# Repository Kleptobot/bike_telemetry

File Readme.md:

# OBike — Open Bicycle Telemetry Platform

OBike is an open-source hardware and firmware project for building a DIY bike computer that feels closer to a purpose-built cycling device than a generic microcontroller project. It combines a colour display, GPS, Bluetooth sensors, barometric altitude, and SD-card logging into a single platform you can build, modify, and improve.

If you like the idea of a compact, open bike computer that can log rides, display live metrics, and be extended with new sensors or UI ideas, this repository is a good place to start.

## What this project does

OBike is intended to capture and present ride data such as:

- speed and distance
- cadence and power
- heart rate
- GPS position and track history
- barometric altitude and sensor-derived data

It presents that information on a colour screen and can log sessions to microSD in FIT, TCX, or CSV formats.

It also supports common Bluetooth cycling peripherals that implement the CSC, HRM, and CPS profiles.

## What is in this repository

- `src/` — firmware source in C++
  - `src/App.*` — main application state and control flow
  - `src/HAL/` — hardware abstraction for GPS, SD, Bluetooth, buttons, and sensors
  - `src/ui/` — UI screens and widgets
  - `src/Loggers/` — FIT, TCX, and CSV logging implementations
  - `src/display/` — display driver and rendering wrappers
- `kicad/` — KiCad schematic and PCB layout files
- `3D_CAD/` — enclosure and mounting CAD files for 3D printing
- `sim/` — desktop simulator for trying the firmware logic without hardware
- `platformio.ini` — PlatformIO build configuration

## Hardware overview

The current hardware target is a compact embedded bike-computer build based on:

- MCU: Seeed Studio XIAO nRF52840 (Sense)
- GNSS: Quectel LC76G module
- Display: ST7789-based full-colour 240×320 SPI panel
- Sensors: RTC, barometric pressure sensor, IMU, and SD card storage
- IO: debounced physical controls and Bluetooth cycling-device support

## Quick start

### Build the firmware

1. Install PlatformIO.
2. From the repository root, run:

   ```bash
   platformio run
   ```

3. To upload to the target board:

   ```bash
   platformio run --target upload
   ```

### Try it without hardware

The repository includes a desktop simulator under `sim/` that can exercise much of the application logic and UI without needing the embedded board.

## Software features

- Firmware built with PlatformIO and the Arduino framework
- Telemetry aggregation from BLE sensors, GPS, and onboard sensors
- Logging to microSD in FIT, TCX, and CSV formats
- GPS control and NMEA handling for the LC76G module
- A simple UI for ride data and device interaction
- Bluetooth device discovery, pairing, and connection management

## Dependencies

The firmware depends on a number of Arduino and embedded libraries, including:

- `Adafruit_GFX`
- `Adafruit_ST7789`
- `MCP23017` support for the I/O expander
- `LSM6DS3`
- `XENSIV` pressure-sensor support
- `ArduinoJson`
- `TinyGPSPlus`
- `teddokano/RTC_NXP_Arduino`

## Key files to inspect

- `src/HAL/LC76G.cpp` and `src/HAL/LC76G.hpp` — GNSS driver, NMEA handling, and command flow
- `src/display/Display.hpp` and `src/display/Display.cpp` — display wrapper and rendering layer
- `src/Loggers/TCXLogger.cpp` and `src/Loggers/CSVLogger.cpp` — ride logging implementations
- `src/App.cpp` — main application loop and state handling
- `kicad/` — schematic and PCB design files
- `3D_CAD/` — printable enclosure and mounting hardware

## Troubleshooting and debugging

- Serial logs are useful during development and can help trace GPS and device activity.
- Raw NMEA data can be captured to the SD card for debugging GPS behavior.
- The LC76G path has previously been sensitive to malformed or long NMEA streams, so keeping firmware updates current is important if you hit GPS issues.

## Notes for first-time visitors

This project is best viewed as a hands-on, open-source bike-computer platform rather than a polished consumer product. It is a strong fit if you want to learn embedded firmware, PCB design, logging formats, BLE peripherals, and how a compact cycling computer can be assembled from open parts.

If you are curious about building your own ride-data device, this repository is a practical starting point for both the hardware and software sides of the project.

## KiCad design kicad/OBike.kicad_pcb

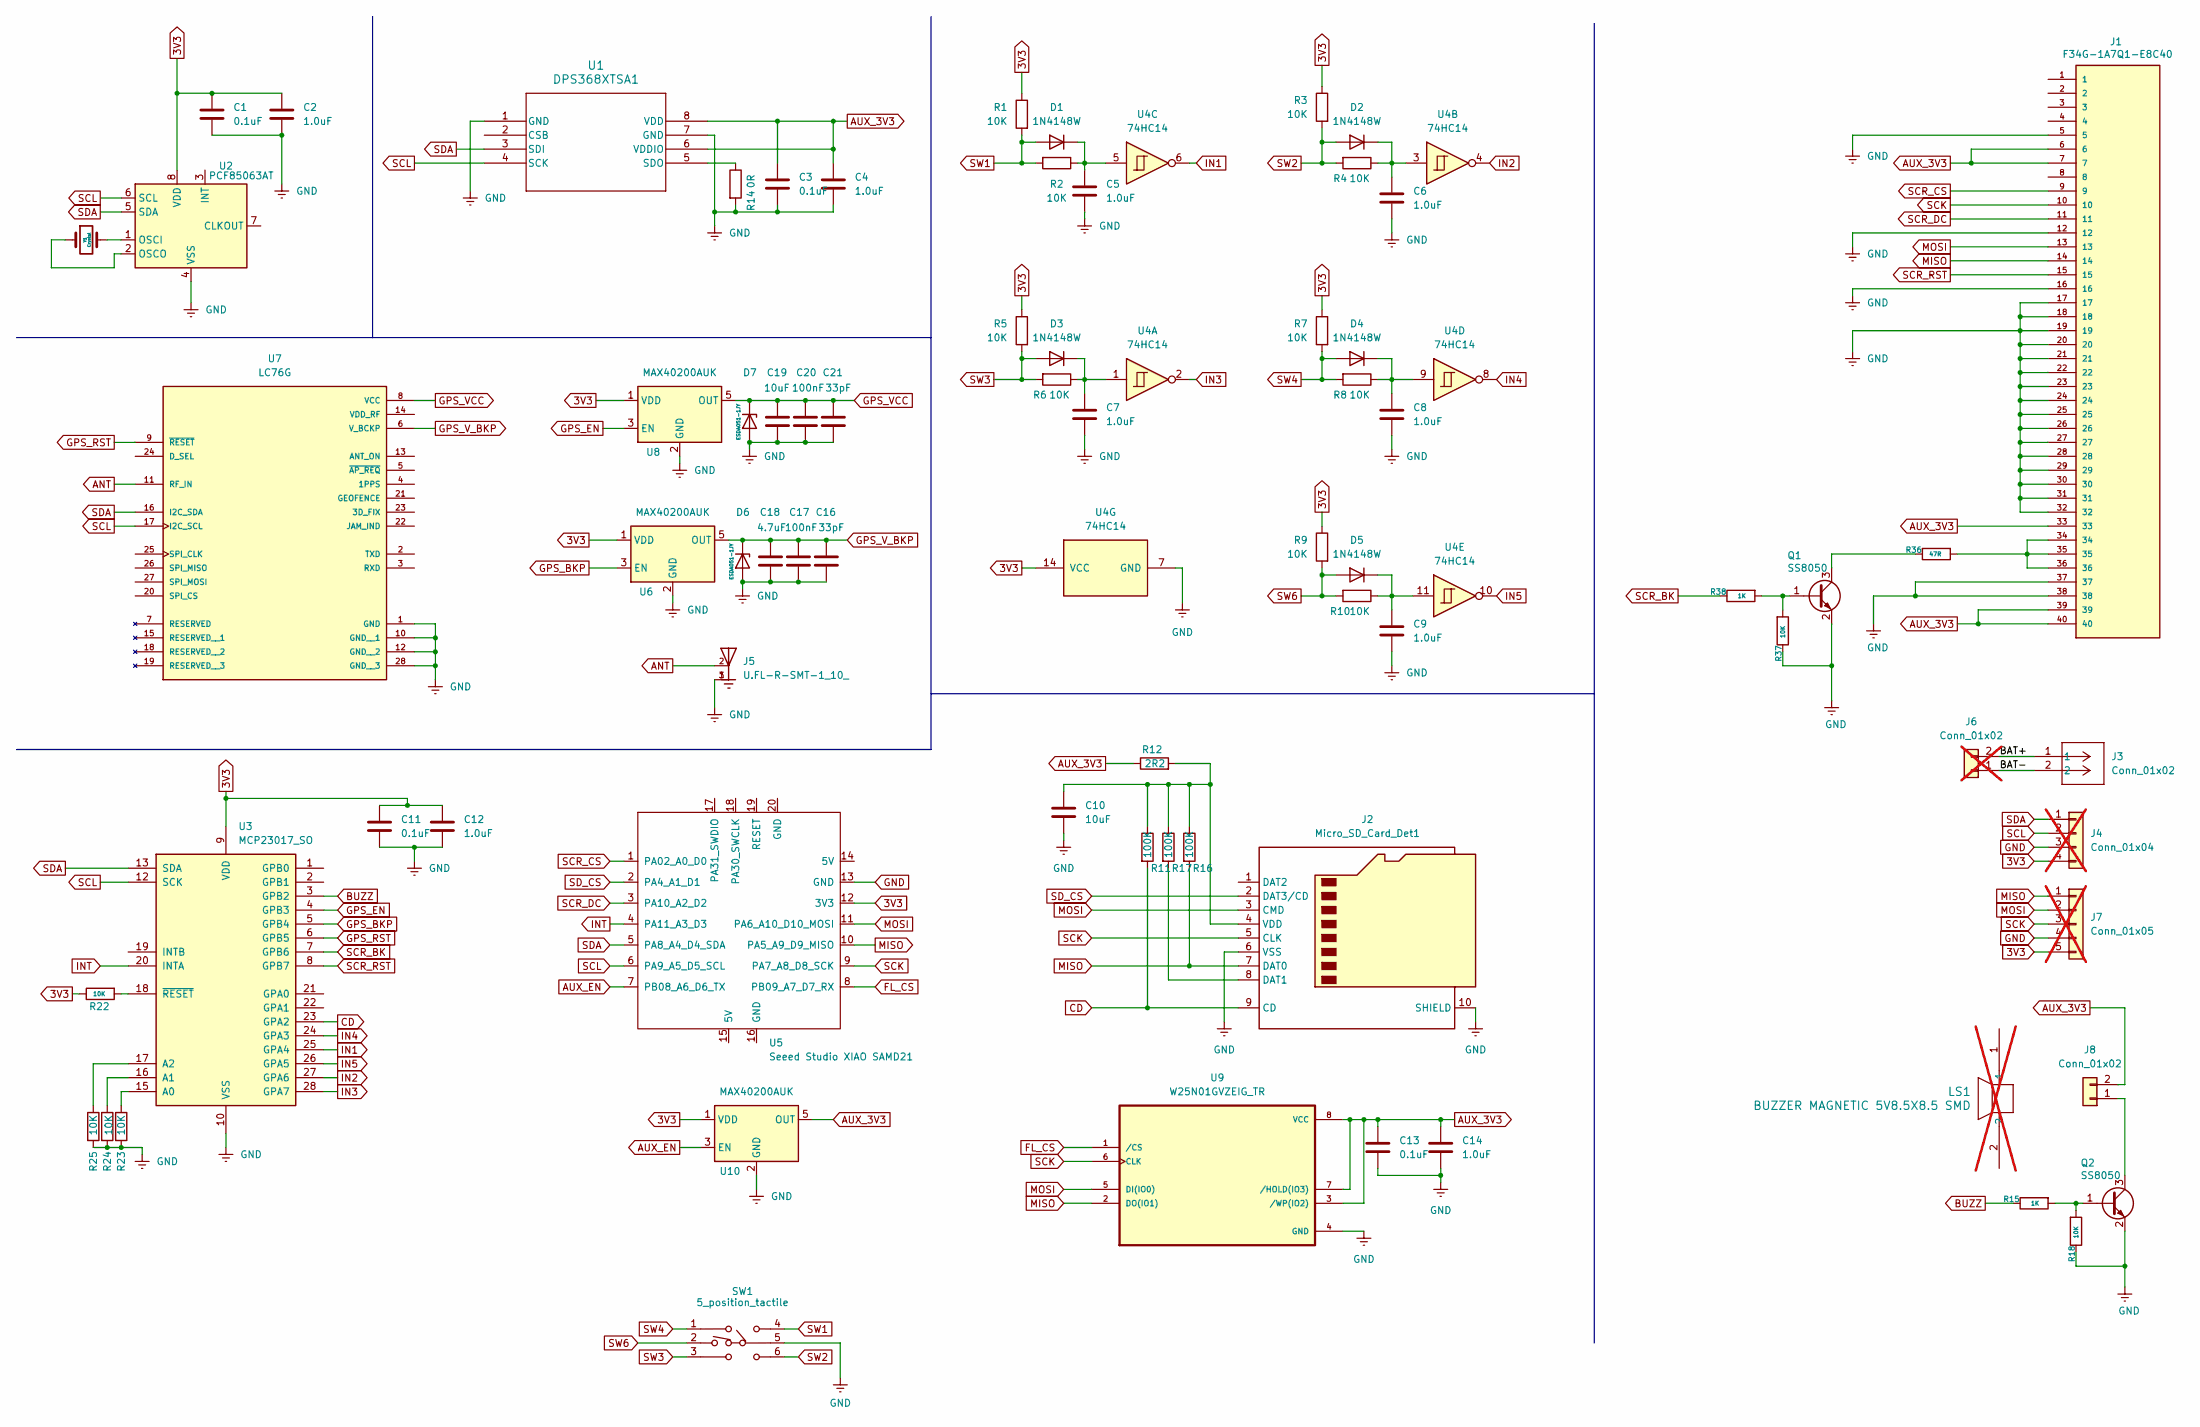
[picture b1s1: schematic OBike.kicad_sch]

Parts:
C1, C3, C11, C13: 0.1uF; C_0805_2012Metric; Digikey PN 1276-2442-1-ND
C2, C4, C5, C6, C7, C8, C9, C12, C14: 1.0uF; C_0805_2012Metric; Digikey PN 1276-1066-1-ND
C10, C19: 10uF; C_0603_1608Metric; Digikey PN 1276-1038-1-ND
C16, C21: 33pF; C_0603_1608Metric; Digikey PN 399-C0603C330K3RACTUCT-ND
C17, C20: 100nF; C_0603_1608Metric; Digikey PN 399-C0603C104K3RACTUCT-ND
C18: 4.7uF; C_0603_1608Metric; Digikey PN 1276-1044-1-ND
D1, D2, D3, D4, D5: 1N4148W; D_SOD-123; Manufacturer PN 1N4148W RHG; Digikey PN 1655-1N4148WCT-ND
D6, D7: ESDA051-1JY; D_SOD-323; Digikey PN 497-ESDA051-1JYCT-ND
J1: F34G-1A7Q1-E8C40; AMPHENOL_F34G-1A7Q1-E8C40; PARTREV A; Digikey PN 609-F34G-1A7Q1-E8C40CT-ND
J2: Micro_SD_Card_Det1; CUI_MSD-4-A; Manufacturer PN MSD-4-A; Digikey PN 2223-MSD-4-ACT-ND
J3: Conn_01x02; JST_PH_S2B-PH-K_1x02_P2.00mm_Horizontal; Manufacturer PN CONN HEADER R/A 2POS 2MM; Digikey PN 455-1719-ND
J4: Conn_01x04; PinHeader_1x04_P2.54mm_Vertical; not fitted
J5: U.FL-R-SMT-1_10_; HRS_U.FL-R-SMT-1_10_; Digikey PN H11891CT-ND
J6: Conn_01x02; PinHeader_1x02_P2.00mm_Vertical; not fitted
J7: Conn_01x05; PinHeader_1x05_P2.54mm_Vertical; not fitted
J8: Conn_01x02; PinHeader_1x02_P2.00mm_Vertical
LS1: BUZZER MAGNETIC 5V8.5X8.5 SMD; CUI_CMT-8540S-SMT; Digikey PN 102-3746-1-ND; not fitted
Q1, Q2: SS8050; SOT-23; Digikey PN MMSS8050-H-TPMSCT-ND
R1, R2, R3, R4, R5, R6, R7, R8, R9, R10, R22, R23, R24, R25: 10K; R_0805_2012Metric; Digikey PN RMCF0805JT10K0CT-ND
R11, R16, R17: 100K; R_0603_1608Metric; Digikey PN RMCF0603FT100KCT-ND
R12: 2R2; R_0603_1608Metric; Digikey PN RMCF0603FT2R20CT-ND
R14: 0R; R_0603_1608Metric
R15, R38: 1K; R_0603_1608Metric; Digikey PN RMCF0603JT1K00CT-ND
R18, R37: 10K; R_0603_1608Metric; Digikey PN RMCF0603JT10K0CT-ND
R36: 47R; R_0603_1608Metric; Digikey PN RMCF0603JT47R0CT-ND
SW1: 5_position_tactile; 5-position; Manufacturer PN 2425755-1; Digikey PN 450-2425755-1CT-ND
U1: DPS368XTSA1; PG-VLGA-8-2_INF; Manufacturer PN DPS368XTSA1; Digikey PN DPS368XTSA1CT-ND
U2: PCF85063AT; SOIC-8_3.9x4.9mm_P1.27mm; Digikey PN 568-12403-1-ND
U3: MCP23017_SO; SOIC-28W_7.5x17.9mm_P1.27mm; Manufacturer PN MCP23017T-E/SO; Digikey PN MCP23017T-E/SOCT-ND
U4: 74HC14; SOIC-14_3.9x8.7mm_P1.27mm; Manufacturer PN 74HC14D; Digikey PN 74HC14DCT-ND
U5: Seeed Studio XIAO SAMD21; XIAO-nRF52840-Sense-14P-2.54-21X17.8MM
U6, U8, U10: MAX40200AUK; SOT-23-5; Digikey PN MAX40200AUK+TCT-ND
U7: LC76G; XCVR_LC76G; PARTREV 1.0; Digikey PN 2958-LC76GPAMDCT-ND
U9: W25N01GVZEIG_TR; SON127P800X600X80-9N; Digikey PN 256-W25N01GVZEIGTRCT-ND
Y1: Crystal; OSCSC320X150X90; Digikey PN 1908-Q0,032768-JTX310-7-20-T3-80K-LFCT-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

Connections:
3V3: C1.1, C2.1, C11.1, C12.1, J4.4, J7.5, R1.1, R3.1, R5.1, R7.1, R9.1, R22.1, U2.8 (VDD), U3.9 (VDD), U4.14 (VCC), U5.12 (3V3), U6.1 (VDD), U8.1 (VDD), U10.1 (VDD)
/BAT+: J3.1, J6.2
/BAT-: J3.2, J6.1
ANT: J5.2, U7.11 (RF_IN)
AUX_3V3: C3.1, C4.1, C13.1, C14.1, J1.6, J1.7, J1.33, J1.39, J1.40, J8.2, R12.1, U1.6 (VDDIO), U1.8 (VDD), U9.3 (/WP(IO2)), U9.7 (/HOLD(IO3)), U9.8 (VCC), U10.5 (OUT)
AUX_EN: U5.7 (PB08_A6_D6_TX), U10.3 (EN)
BUZZ: R15.1, U3.3 (GPB2)
CD: J2.9 (CD), R11.2, U3.23 (GPA2)
FL_CS: U5.8 (PB09_A7_D7_RX), U9.1 (/CS)
GND: C1.2, C2.2, C3.2, C4.2, C5.2, C6.2, C7.2, C8.2, C9.2, C10.2, C11.2, C12.2, C13.2, C14.2, C16.2, C17.2, C18.2, C19.2, C20.2, C21.2, D6.2 (A), D7.2 (A), J1.5, J1.12, J1.16, J1.17, J1.18, J1.19, J1.20, J1.21, J1.22, J1.23, J1.24, J1.25, J1.26, J1.27, J1.28, J1.29, J1.30, J1.31, J1.32, J1.37, J1.38, J2.6 (VSS), J2.10 (SHIELD), J4.3, J5.1, J5.3, J7.4, Q1.2 (E), Q2.2 (E), R14.2, R18.1, R23.2, R24.2, R25.2, R37.1, SW1.5 (E), U1.1 (GND), U1.7 (GND), U2.4 (VSS), U3.10 (VSS), U4.7 (GND), U5.13 (GND), U6.2 (GND), U7.1 (GND), U7.10 (GND__1), U7.12 (GND__2), U7.28 (GND__3), U8.2 (GND), U9.4 (GND), U10.2 (GND)
GPS_BKP: U3.5 (GPB4), U6.3 (EN)
GPS_EN: U3.4 (GPB3), U8.3 (EN)
GPS_RST: U3.6 (GPB5), U7.9 (~RESET)
GPS_VCC: C19.1, C20.1, C21.1, D7.1 (K), U7.8 (VCC), U8.5 (OUT)
GPS_V_BKP: C16.1, C17.1, C18.1, D6.1 (K), U6.5 (OUT), U7.6 (V_BCKP)
IN1: U3.25 (GPA4), U4.6
IN2: U3.27 (GPA6), U4.4
IN3: U3.28 (GPA7), U4.2
IN4: U3.24 (GPA3), U4.8
IN5: U3.26 (GPA5), U4.10
INT: U3.20 (INTA), U5.4 (PA11_A3_D3)
MISO: J1.14, J2.7 (DAT0), J7.1, R16.2, U5.10 (PA5_A9_D9_MISO), U9.2 (DO(IO1))
MOSI: J1.13, J2.3 (CMD), J7.2, U5.11 (PA6_A10_D10_MOSI), U9.5 (DI(IO0))
unnamed: C5.1, D1.1 (K), R2.1, U4.5
unnamed: C6.1, D2.1 (K), R4.1, U4.3
unnamed: C7.1, D3.1 (K), R6.1, U4.1
unnamed: C8.1, D4.1 (K), R8.1, U4.9
unnamed: C9.1, D5.1 (K), R10.1, U4.11
unnamed: J1.34, J1.35, J1.36, R36.2
unnamed: J2.8 (DAT1), R17.2
unnamed: C10.1, J2.4 (VDD), R11.1, R12.2, R16.1, R17.1
unnamed: J8.1, Q2.3 (C)
unnamed: Q1.1 (B), R37.2, R38.2
unnamed: Q1.3 (C), R36.1
unnamed: Q2.1 (B), R15.2, R18.2
unnamed: R14.1, U1.5 (SDO)
unnamed: U2.1 (OSCI), Y1.2
unnamed: U2.2 (OSCO), Y1.1
unnamed: R23.1, U3.15 (A0)
unnamed: R24.1, U3.16 (A1)
unnamed: R25.1, U3.17 (A2)
unnamed: R22.2, U3.18 (~RESET)
SCK: J1.10, J2.5 (CLK), J7.3, U5.9 (PA7_A8_D8_SCK), U9.6 (CLK)
SCL: J4.2, U1.4 (SCK), U2.6 (SCL), U3.12 (SCK), U5.6 (PA9_A5_D5_SCL), U7.17 (I2C_SCL)
SCR_BK: R38.1, U3.7 (GPB6)
SCR_CS: J1.9, U5.1 (PA02_A0_D0)
SCR_DC: J1.11, U5.3 (PA10_A2_D2)
SCR_RST: J1.15, U3.8 (GPB7)
SDA: J4.1, U1.3 (SDI), U2.5 (SDA), U3.13 (SDA), U5.5 (PA8_A4_D4_SDA), U7.16 (I2C_SDA)
SD_CS: J2.2 (DAT3/CD), U5.2 (PA4_A1_D1)
SW1: D1.2 (A), R1.2, R2.2, SW1.4 (D)
SW2: D2.2 (A), R3.2, R4.2, SW1.6 (F)
SW3: D3.2 (A), R5.2, R6.2, SW1.3 (C)
SW4: D4.2 (A), R7.2, R8.2, SW1.1 (A)
SW6: D5.2 (A), R9.2, R10.2, SW1.2 (B)

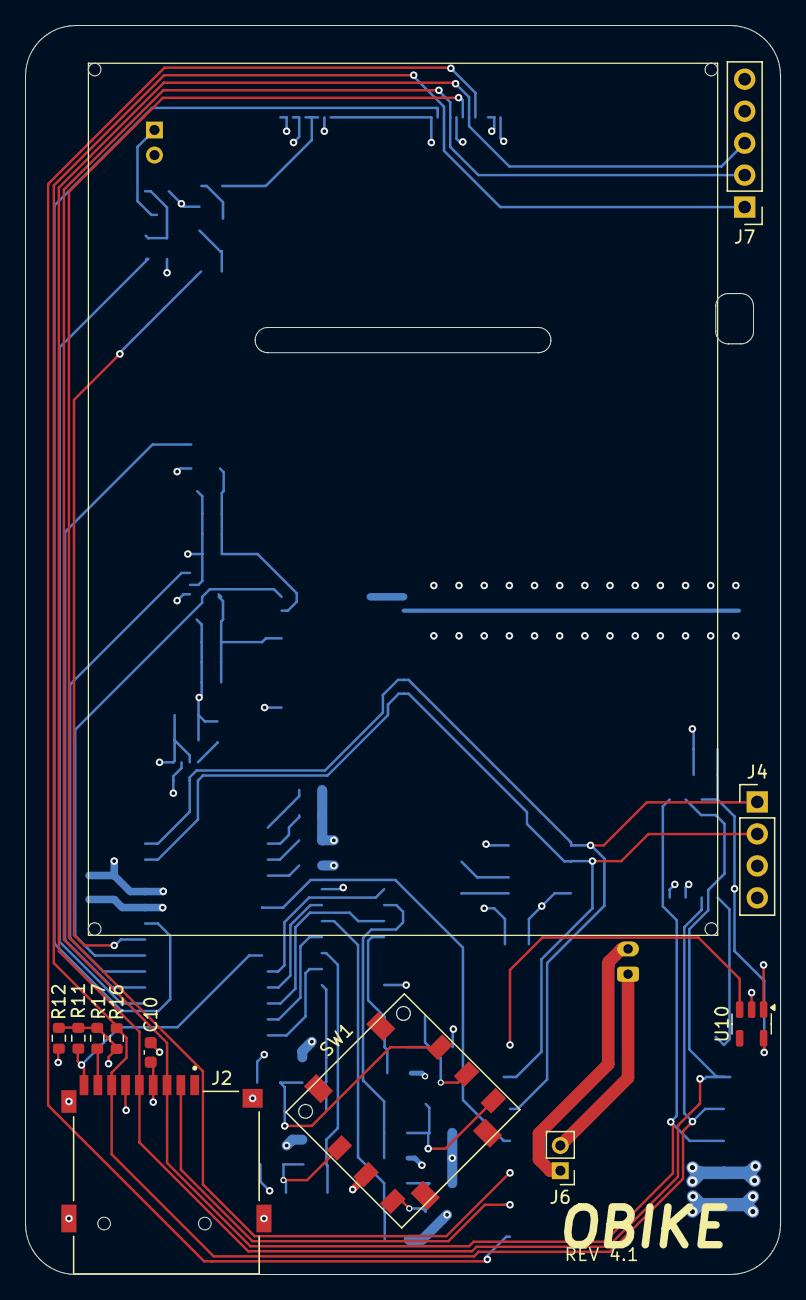
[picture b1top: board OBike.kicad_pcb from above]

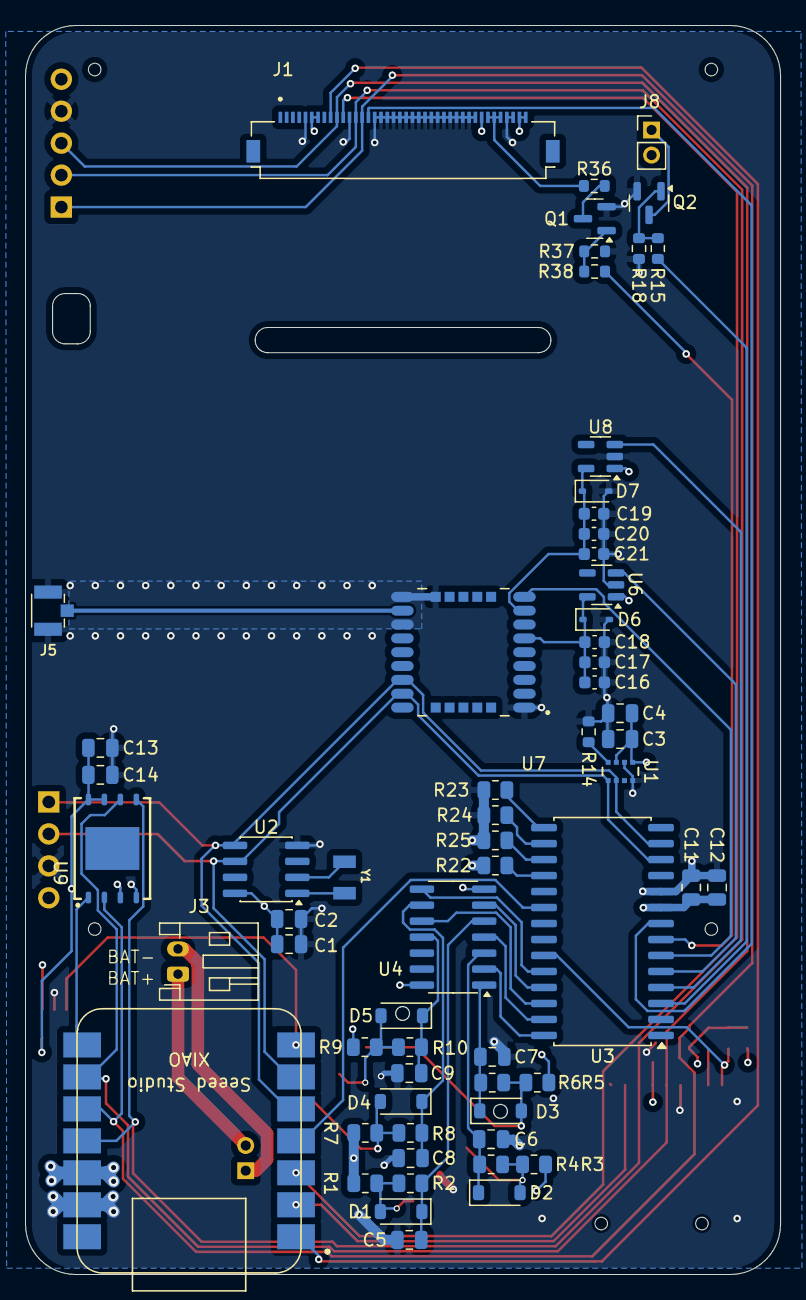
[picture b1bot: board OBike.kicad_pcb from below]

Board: 4 copper layers, 60.0 x 99.2 mm, 73 parts (62 on the bottom side), 55 nets.

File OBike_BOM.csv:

"Reference","Value","Datasheet","Footprint","Qty","DNP","PARTREV","Manufacturer PN","Manufacturer","Digikiey PN"
"AE1","Antenna","~","Antenna:AC30036-01","1","","","AC30036-01","The Antenna Company","5350-AC30036-01-ND"
"C1,C3,C11","0.1uF","~","Capacitor_SMD:C_0805_2012Metric","3","","","","",""
"C2,C4,C5,C6,C7,C8,C9,C12","1.0uF","~","Capacitor_SMD:C_0805_2012Metric","8","","","","",""
"C10","10uF","~","Capacitor_SMD:C_0603_1608Metric","1","","","","",""
"D1,D2,D3,D4,D5","1N4148W","https://www.vishay.com/docs/85722/1n4448w.pdf","Diode_SMD:D_SOD-123","5","","","1N4148W RHG","Taiwan Semiconductor Corporation","1N4148WRHGCT-ND"
"J1","Conn_01x08","~","Connector_JST:JST_GH_SM08B-GHS-TB_1x08-1MP_P1.25mm_Horizontal","1","","","","",""
"J2","Micro_SD_Card_Det1","https://datasheet.lcsc.com/lcsc/2110151630_XKB-Connectivity-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","CUI-devices:CUI_MSD-11-A","1","","","MSD-11-A","Same Sky (Formerly CUI Devices)","2223-MSD-11-ACT-ND"
"J3,J6","Conn_01x02","-- mixed values --","-- mixed values --","2","","","-- mixed values --","-- mixed values --","-- mixed values --"
"R1,R2,R3,R4,R5,R6,R7,R8,R9,R10,R16,R22,R23,R24,R25","10K","~","-- mixed values --","15","","","","",""
"R11,R15,R17","100K","~","Resistor_SMD:R_0603_1608Metric","3","","","","",""
"R12","2R2","~","Resistor_SMD:R_0603_1608Metric","1","","","","",""
"R13,R14","0R","~","Resistor_SMD:R_0603_1608Metric","2","","","","",""
"SW1","5_position_tactile","~","5_pos:5-position","1","","","2425755-1","TE Connectivity ALCOSWITCH Switches","450-2425755-1CT-ND"
"U1","DPS368XTSA1","DPS368XTSA1","Infineon Technologies:PG-VLGA-8-2_INF","1","","","DPS368XTSA1","Infineon Technologies","DPS368XTSA1CT-ND"
"U2","DS3231M","http://datasheets.maximintegrated.com/en/ds/DS3231.pdf","Package_SO:SOIC-8_3.9x4.9mm_P1.27mm","1","","","DS3231MZ+","Analog Devices Inc./Maxim Integrated","DS3231MZ+-ND"
"U3","MCP23017_SO","http://ww1.microchip.com/downloads/en/DeviceDoc/20001952C.pdf","Package_SO:SOIC-28W_7.5x17.9mm_P1.27mm","1","","","MCP23017T-E/SO","Microchip Technology","MCP23017T-E/SOCT-ND"
"U4","74HC14","http://www.ti.com/lit/gpn/sn74HC14","Package_SO:SOIC-14_3.9x8.7mm_P1.27mm","1","","","74HC14D","Toshiba Semiconductor and Storage","74HC14DCT-ND"
"U5","Seeed Studio XIAO SAMD21","","xiao:XIAO-nRF52840-Sense-14P-2.54-21X17.8MM","1","","","","",""
"U6","MAX-M8C-0","","uBlox:XCVR_MAX-M8C-0","1","","R06, 27-May-2020","MAX-M8C-0","u-blox","672-MAX-M8C-0CT-ND"

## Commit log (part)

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2024-04-30 Initial code checkin
2024-04-30 electrical
2024-04-30 renaming .ino
2024-04-30 renaming folder structure
2024-04-30 adding millis to logging
2024-06-29 kicad libraries
    added symbols and footprints.
    put library files in dedicated folder
2024-06-29 Added PCB files
    added kicad project files
2024-06-29 License and Readme
    added the readme file updated license
2024-06-29 fixing pcb references
    changed references to combined board to Obike in the PCB file
2024-06-29 Readme to markdown
2024-06-29 1.69" TFT
    Changed screen connections to suit an SPI screen
    Changed the arduino project to use the adafruit ST7789 library
    Intended LCD is the wavshare 1.69" LCD
2024-07-01 adding dsp368 to project
2024-07-12 moved setup back into setup
2024-07-12 sh1107
2024-07-22 using SDFat library now
    log files are now named the datastamp of when the log was started
2024-07-23 bugfixes
    fixed bug where speed available and cadence available where not set to 0 on csc begin
    added timer to main screen when logging
    seperated out devices init into seperate function that is only called if the wake interrupt has been triggered
    cadence now displayed as an integer
2024-07-24 fixed logging bug
    fixed bug that stopped data being written to log
    added functions to write tail data at the end of a log
    now calculate average and max speed
    using the sd card detection pin to reinit sd card when re-inserted
2024-08-05 bug fixes
    added lost power time reset for rtc
    changed device save file to json
    added delay after power on before loading devices from SD
    now wait a bit between connecting to multiple devices
    split draw method and ui method for BT screen
    bt devices now remain selected for storage
2024-08-07 batt disp
    added battery service to csc class
    added logging to sd card
    battery now displays on bt menu
    can now turn off obike by holding down button
2024-08-10 connection issue fix
    - fixed up scanning logic so start scan is not being called too often
    - connection and battery symbols only displayed for stored devices
    - stored symbol does not display for non stored devices
    - connection handle is stored for discovered devices
    - added disconnect callback
    - logger can now accept strings
2024-08-12 Update bike_telemetry.ino
    support for more devices in bt devices view
2024-08-18 BT device polymorphism
    Created base class of BT_Device
    csc now extends BT_Device
    created hrm class which extends BT_Device
2024-08-20 Added cps
    fixed bugs in BT_Device implementation
2024-08-25 Bug fixing
    removing BT devices no longer causes crashes
    upped the number of data sources able to be logged
    changed most uses of String to char*
    heartrate now shows on main screen
2024-08-25 device scanning fixes
    scanning now starts for stored devices
    discovered devices now identified as the correct type
    hrm battery service now started correctly
2024-09-01 moved SD instance to main
    SD instance is now in the main sketch
    logger now takes a pointer to SD
    removed the logging to SD card
    logger now longer closes file between entries
2024-10-09 GPS code added
    just reading into variables and printing to console for now
2024-10-10 TCX file format
    write both csv and tcx files now
2024-10-10 tcx logging fixes
2024-12-08 gps added
2024-12-10 antennae
2025-01-15 gps 4-layer
2025-01-25 SD init & GPS read
    display updates every 100ms now
    user input RE and FE update with display
    GPS read now limited to 500ms
2025-01-25 increased GPS precision
2025-01-30 UI changes
2025-01-30 added GPS power management
2025-01-31 menu fixes
2025-01-31 removed list lib
    also fixed some GPS power stuff
2025-02-13 Added CPS notify
    also fixed some GPS power state stuff.
    added some flushes to the TPX logger to try and eliminate corruption
2025-02-24 GPS power options
    - GPS settings menu, with save load to JSON on SD card
    - Ublox PM2 methods
    - UBlox GPS settings object
2025-04-25 UI refactor
    - created button and menu classes
    - moved menu code into seperate files
    - moved GUI draw methods into seperate file
2025-05-08 stopper using logger
    also some fixes for tcx
2025-05-19 re wrote TCX logger
2025-05-22 quectel module
    changed gps module
    increased board size
    moved gps module to front bottom left
    moved sd card front bottom right
2025-05-26 tcxLogger fixes
    changed functions to take poiters to Fil32 not a copy (duh)
2025-07-28 rev 3 pcb
    - quectel gps
    - u.fl antenae conn
    - aux power switch
    - flash chip
2025-08-17 file writing
2025-08-17 rev 3 pcb
2025-09-16 Purchased PCBs
2025-09-16 Button class
2025-09-17 Menu interaction classes
    - created TimeMenu class
    - created body class
    - created GUI header file define global draw methods
2025-09-17 bodyStats
    age now based on birthday
2025-10-25 migrate to platform IO
2025-10-25 data providers
2025-10-26 screens
    created the screens
    listView is a lot better now
    removed old files
    updated App to change its state on events
    App state is now part of the data model
2025-10-29 biometric screen
2025-11-02 app working
    - App now owns the UIManager instance
    - UIManager now sets the eventBus reference in the screens when they're registered
    - tcx logger now aware of the data model
    - app.update called in main
2025-11-04 EditDisplayScreen
2025-11-04 LayoutDataProvider
2025-11-04 cleaning up old files
2025-11-04 BT device discovery
    - bt device system correctly starting in boot
    - added some debug messages
    - BT_Device::discovered function correctly overriden by children
2025-11-06 LCD interface
    fixed mistakes in FPC connector nets
2025-11-15 lots of ui fixes
2025-11-15 ui fixes and optimisation
2025-11-16 more ui fixes
    starting to look ok
2025-11-16 more ui fixes
2025-11-17 more display configuration
2025-11-20 screen fpc
    - changed fpc to bottom mount pins
    - changed fpc footprint and symbol
    - updated fpc routing
    - added JST connectors for SPI & I2C expansion
    - stopped tracking kicad/*.zip
2025-11-20 removing zips
2025-11-22 gps distance
    - now use the Haversine formula to calculate distance traveled from gps coord
    - calc is performed in the app
2025-11-25 better filtering for BT devices
    - also some ui fixes
    - added missing art
    - added GPS settings screen
2025-12-08 pcb update
2025-12-13 buzzer
2025-12-14 BT fixes
    - BT screen now displays devices correctly
    - BT disconnect/connect from UI working
    - fixed missing break in APP DisconnectBluetooth event case
    - added lower and upper bound protection on Display flush
    - aux supply turns off when system sleeps
2025-12-14 BT fixes
2025-12-14 div by zero protection
2025-12-14 BT device saving
2025-12-14 retry on storage init
2025-12-14 GPS screen nav
2025-12-15 fixed accumulating calcs
    - avg heartrate now more accurate (still not great)
    - avg cadence now more accurate (still not great)
    - telemetry now accumulates distance
2025-12-16 Speed displays correctly
    If there was no other speed source the GPS speed would not get included in the speed average
2025-12-16 BT sources removed on disconnect
    csc and hrm values of disconnected devices not used in average caluclations
2025-12-16 not all BT devices displayed
    missing update callback on BT load devices
2025-12-16 display small values
    - data widget now displays 1 decimal place for values < 10
    - tweaked how the telemetry data provider accumulates distance
2025-12-29 NMEA responses
    - HAL no longer has static members
    - LC76G class now manages NMEA sentences
    - LC76G class can fire callbacks when expected response seen
    - HAL no longer cares about LC76G state
    -
2026-01-02 More LC76G abstraction
    - now use encode decode functions in command defs
    - responses can have their payloads decoded
2026-01-04 LC76G driver
    - more sentence encoders
    - more sentence decoders
    - log NMEA sentences to file
    - more commands defined
2026-05-28 updates to gps menu
    added location as telemetry type for data widget
2026-05-30 reusing existing members for location data in telemetry provider
2026-05-30 fixes for ui glitches
2026-06-05 UI rendering improvements
    - only redrawing data widgets when they get a new value
    - only setting icons in main screen on state change
    - toggleable debug messages
2026-06-05 UI render throttle
    - UI renders every 100ms now
    - date and time widgets now support held presses to rapidly change selection
    - widget list now supports held press to rapidly change focus
2026-06-05 buttons use references not pointer
2026-06-05 Batt in telemetry
    Batt percentage is being passed into the telemetry data model now
2026-06-06 NMEA rates
    - fixed typo in NMEA rate messages
    - App now turns off all NMEA messages except RMC and GGA
    - added buffer protection to NMEA message access
    - main screen updates battery value
    - battery widget only invalidates on new value
    - reduced sensor update rates
2026-06-06 gps logging now conditional
2026-06-07 PCB speaker
    - buzzer now uses a header rather than SMD
    - added buzzer code to HAL
    - small fixes to tcx logger
2026-06-07 convert tiles from png to raw
2026-06-07 added map widget
2026-06-07 maps test
2026-06-07 git ignore update
2026-06-07 Added HR zones
2026-06-07 some debug messages in BT
2026-06-07 more efficient display
    - update or replace existing rects in display
2026-06-08 GPS screen update
    - all message type rates now accessible from GPS screen
    - fixed problem with erroneous button presses on startup
    - SD card detection state now used, detect insert and reload files
    - fixed compiler warnings
    - save NOVRAM now working
2026-06-09 SD card unmount
2026-06-09 schem updates
    - added locating holes for screen to PCB
2026-06-10 housing stl's
2026-06-10 gerbers and pcb render
2026-06-10 GPS time sync
    - now read gpsTime on fix
    - if rtc time is too far from gps time, auto adjust RTC
    - UTC offset stored in biometrics.txt for now
    - updated readme with more deps too
2026-06-10 time syncing working
2026-06-11 updated part numbers
2026-06-11 fixed typo in part number fields
2026-06-11 zenners went EOL updated to new device
2026-06-23 new timeData struct
2026-06-24 BT device disconnect now updates deviceList connected state
2026-06-25 New duration widget
    - Durations now have a dedicated widget
    - fixed bug in csc where non update case was not accounted for
    - fixed small bug in TCX logger which caused negative lap times to briefly appear
2026-06-25 totalHours timeDuration
2026-06-26 I am the linter!
2026-06-27 added FIT file support
2026-06-27 re activating RMC messages
2026-06-28 FIT CRC
    - fixed FIT CRC calc
    - moved string methods for lap times into logger interface
    - fixed FIT headers not being written on concurrent activities
2026-06-28 SD timestamps
    - added dateTime callback to SDCardSystem
    - HAL now passes address of rtc object to SDCardSystem on init
    - moved time save/load out of biometrics into separate file and methods
2026-06-28 local time SD card time stamps
